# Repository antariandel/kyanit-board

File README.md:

# __Kyanit__ Board

## Introduction

Kyanit Board is part of the Kyanit ecosystem. See https://github.com/kyanit-project/kyanit for an
introduction to Kyanit.

Kyanit Board is the official Kyanit Core-compatible ESP8266-based controller board designed to be
used for home automation.

## The Kyanit Ecosystem

* [**Kyanit Core**](https://github.com/kyanit-project/kyanit)

The core Kyanit module, flashed into an ESP8266 board.

* [**Kyanit Board**](https://github.com/kyanit-project/kyanit-board)

This repo. A stylish, triangle-shaped ESP8266-based board built around an ESP-12F module, the
official Kyanit controller board.

* [**Kyanit CTL**](https://github.com/kyanit-project/kyanit-ctl)

Command-line utility for interacting with Kyanit.

* [**Kyanit API**](https://github.com/kyanit-project/kyanit-api)

Python API for interaction with Kyanit from Python code. (It is used by Kyanit CTL.)

## Board Files

The board is designed in KiCAD and is currently under development. First release to come soon...

## License Notice

Copyright (C) 2020 Zsolt Nagy

This program is free software: you can redistribute it and/or modify it under the terms of the
GNU General Public License as published by the Free Software Foundation, version 3 of the License.

This program is distributed in the hope that it will be useful, but WITHOUT ANY WARRANTY; without
even the implied warranty of MERCHANTABILITY or FITNESS FOR A PARTICULAR PURPOSE.
See the GNU General Public License for more details.
You should have received a copy of the GNU General Public License along with this program.
If not, see <https://www.gnu.org/licenses/>.

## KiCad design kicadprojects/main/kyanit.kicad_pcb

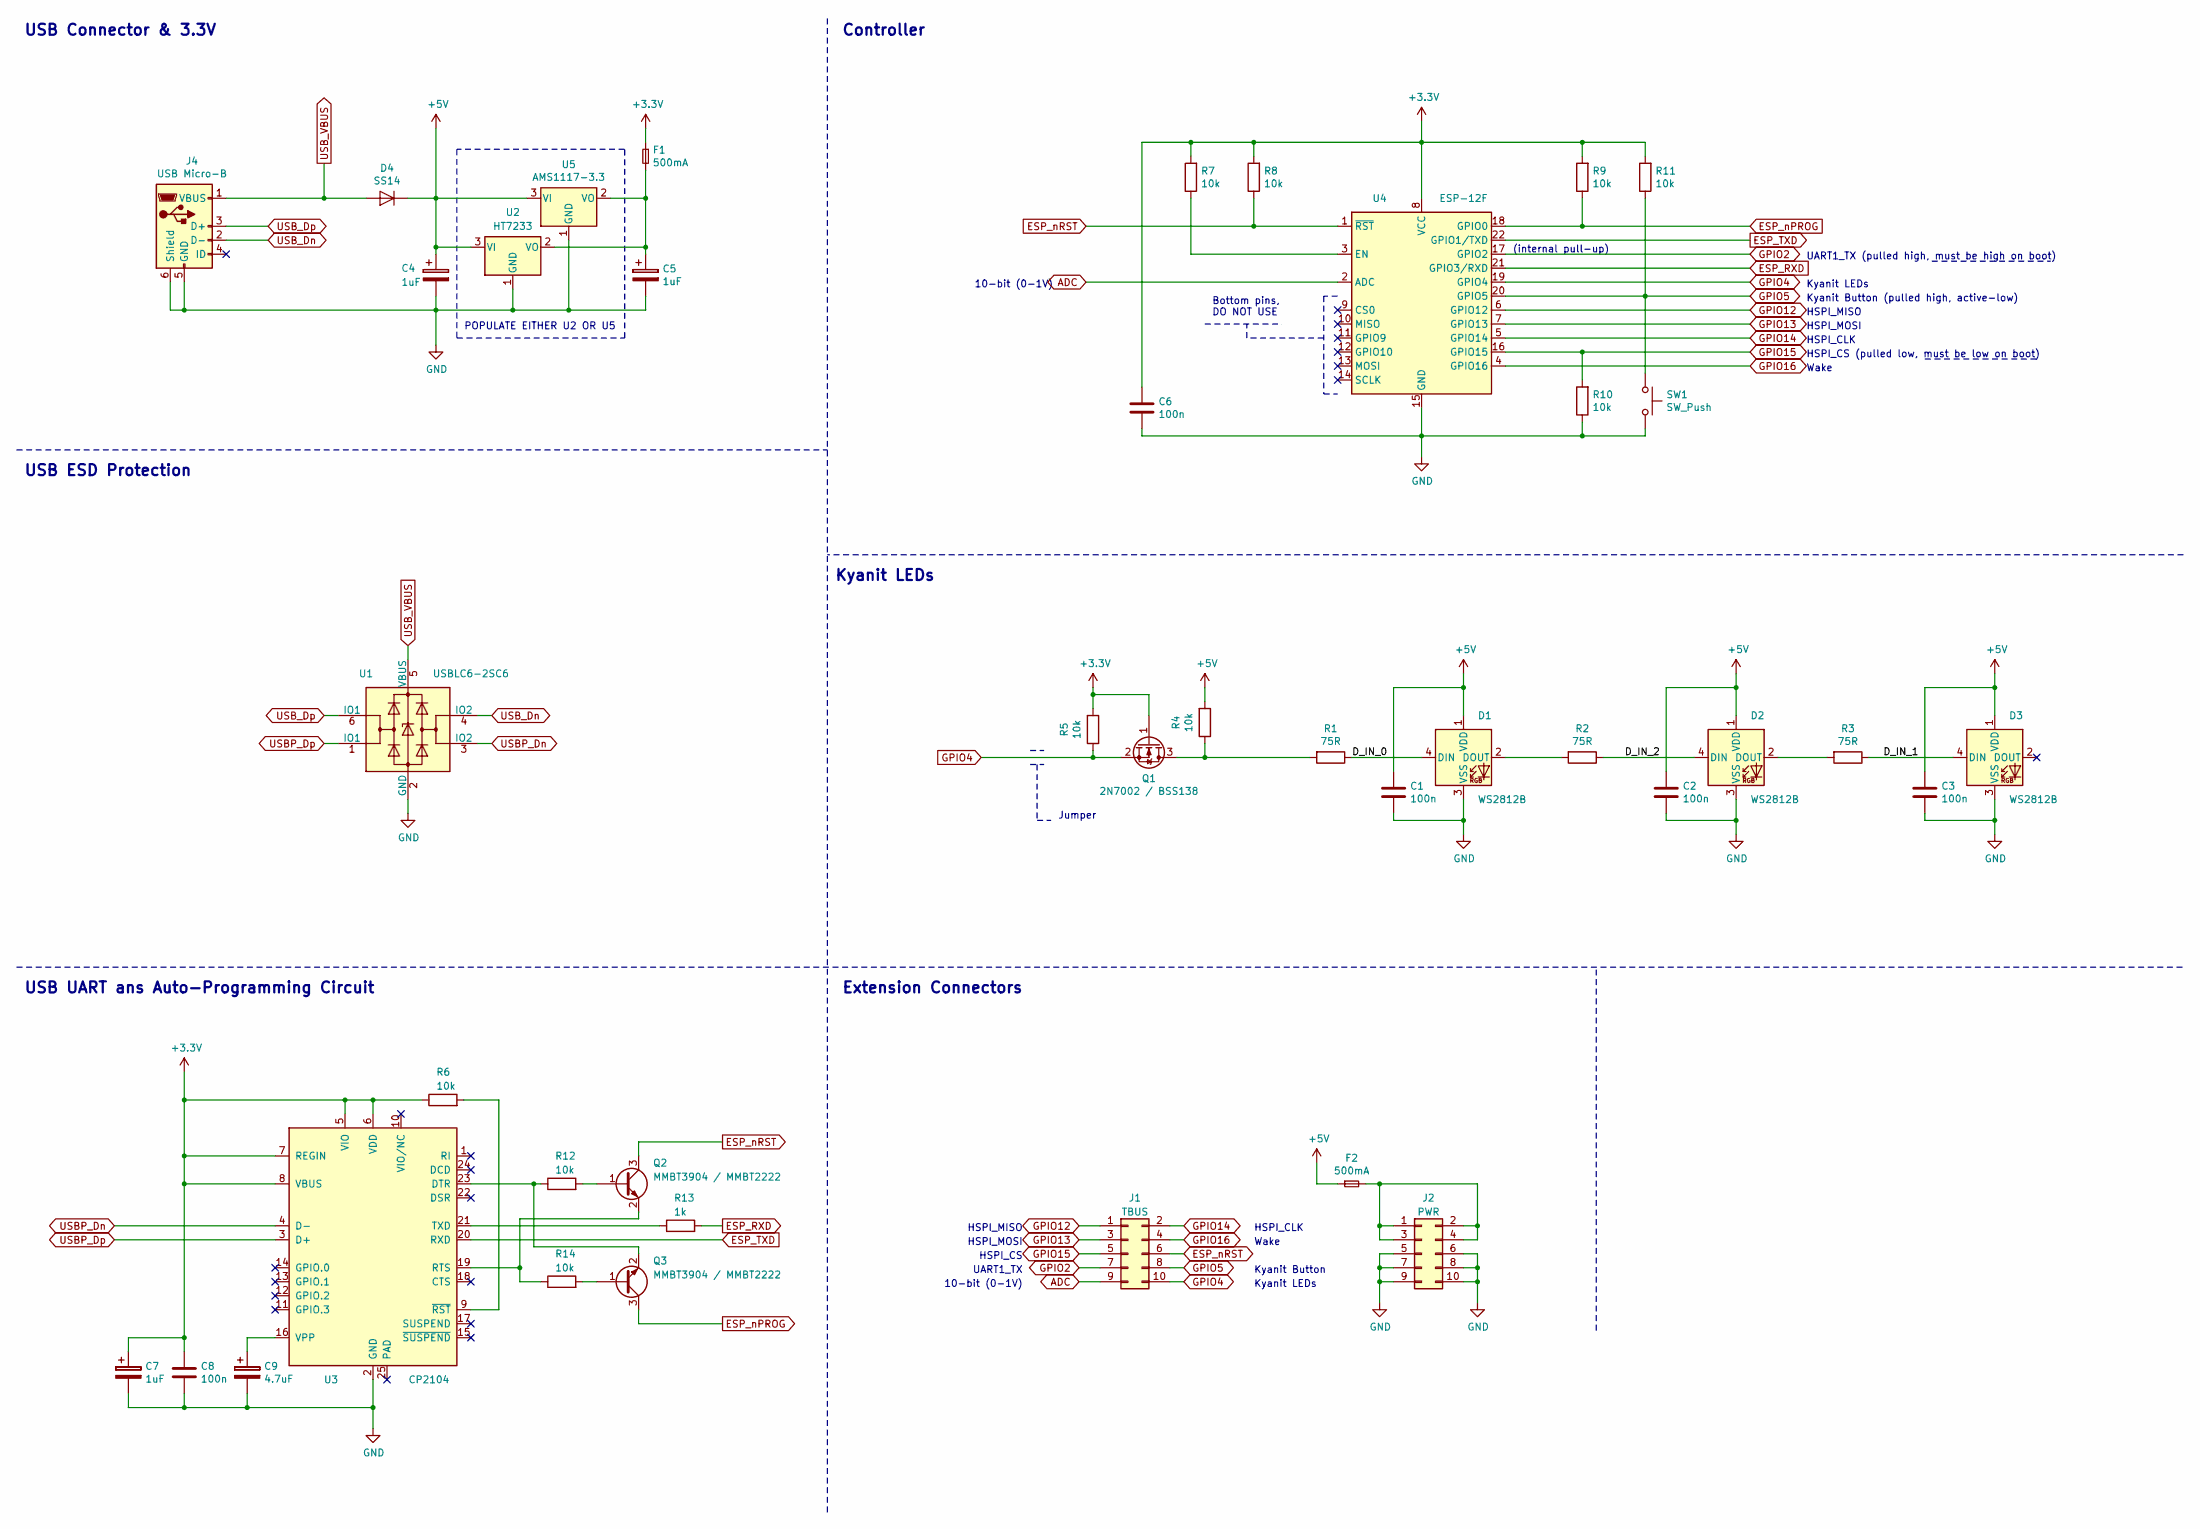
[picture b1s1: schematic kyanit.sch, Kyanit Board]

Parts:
C1, C2, C3, C6, C8: 100n; C_0603_1608Metric_Pad1.05x0.95mm_HandSolder
C4, C5, C7: 1uF; C_1206_3216Metric_Pad1.42x1.75mm_HandSolder
C9: 4.7uF; C_1206_3216Metric_Pad1.42x1.75mm_HandSolder
D1, D2, D3: WS2812B; LED_WS2812B_PLCC4_5.0x5.0mm_P3.2mm
D4: SS14; D_SMA
F1, F2: 500mA; Fuse_1206_3216Metric_Pad1.42x1.75mm_HandSolder
J1: TBUS; PinHeader_2x05_P2.54mm_Vertical
J2: PWR; PinHeader_2x05_P2.54mm_Vertical
J4: USB Micro-B; USB_Micro-B_Molex_47346-0001
Q1: 2N7002 / BSS138; SOT-23
Q2, Q3: MMBT3904 / MMBT2222; SOT-23
R1, R2, R3: 75R; R_0603_1608Metric_Pad1.05x0.95mm_HandSolder
R4, R5, R6, R7, R8, R9, R10, R11, R12, R14: 10k; R_0603_1608Metric_Pad1.05x0.95mm_HandSolder
R13: 1k; R_0603_1608Metric_Pad1.05x0.95mm_HandSolder
SW1: SW_Push; SW_SPST_EVPBF
U1: USBLC6-2SC6; SOT-23-6
U2: HT7233; SOT-23
U3: CP2104; QFN-24-1EP_4x4mm_P0.5mm_EP2.6x2.6mm
U4: ESP-12F; ESP-12E
U5: AMS1117-3.3; SOT-223-3_TabPin2

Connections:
+3V3: C6.1, C7.1, C8.1, F1.1, Q1.1 (G), R5.2, R6.1, R7.2, R8.2, R9.2, R11.2, U3.5 (VIO), U3.6 (VDD), U3.7 (REGIN), U3.8 (VBUS), U4.8 (VCC)
+5V: C1.1, C2.1, C3.1, C4.1, D1.1 (VDD), D2.1 (VDD), D3.1 (VDD), D4.1 (K), F2.1, R4.2, U2.3 (VI), U5.3 (VI)
/D_IN_0: D1.4 (DIN), R1.1
/D_IN_1: D3.4 (DIN), R3.1
/D_IN_2: D2.4 (DIN), R2.1
ADC: J1.9, U4.2 (ADC)
ESP_RXD: R13.2, U4.21 (GPIO3/RXD)
ESP_TXD: U3.20 (RXD), U4.22 (GPIO1/TXD)
ESP_nPROG: Q3.3 (C), R9.1, U4.18 (GPIO0)
ESP_nRST: J1.6, Q2.3 (C), R8.1, U4.1 (~RST)
GND: C1.2, C2.2, C3.2, C4.2, C5.2, C6.2, C7.2, C8.2, C9.2, D1.3 (VSS), D2.3 (VSS), D3.3 (VSS), J2.5, J2.6, J2.7, J2.8, J2.9, J2.10, J4.5 (GND), J4.6 (Shield), R10.1, SW1.2, U1.2 (GND), U2.1 (GND), U3.2 (GND), U4.15 (GND), U5.1 (GND)
GPIO2: J1.7, U4.17 (GPIO2)
GPIO4: J1.10, Q1.2 (S), R5.1, U4.19 (GPIO4)
GPIO5: J1.8, R11.1, SW1.1, U4.20 (GPIO5)
GPIO12: J1.1, U4.6 (GPIO12)
GPIO13: J1.3, U4.7 (GPIO13)
GPIO14: J1.2, U4.5 (GPIO14)
GPIO15: J1.5, R10.2, U4.16 (GPIO15)
GPIO16: J1.4, U4.4 (GPIO16)
unnamed: C5.1, F1.2, U2.2 (VO), U5.2 (VO)
unnamed: C9.1, U3.16 (VPP)
unnamed: D1.2 (DOUT), R2.2
unnamed: D2.2 (DOUT), R3.2
unnamed: F2.2, J2.1, J2.2, J2.3, J2.4
unnamed: Q1.3 (D), R1.2, R4.1
unnamed: Q2.1 (B), R12.2
unnamed: Q2.2 (E), R14.1, U3.19 (RTS)
unnamed: Q3.1 (B), R14.2
unnamed: Q3.2 (E), R12.1, U3.23 (DTR)
unnamed: R6.2, U3.9 (~RST)
unnamed: R7.1, U4.3 (EN)
unnamed: R13.1, U3.21 (TXD)
USBP_Dn: U1.3 (IO2), U3.4 (D-)
USBP_Dp: U1.1 (IO1), U3.3 (D+)
USB_Dn: J4.2 (D-), U1.4 (IO2)
USB_Dp: J4.3 (D+), U1.6 (IO1)
USB_VBUS: D4.2 (A), J4.1 (VBUS), U1.5 (VBUS)

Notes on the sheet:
USB Connector & 3.3V
USB ESD Protection
USB UART ans Auto-Programming Circuit
Extension Connectors
Kyanit LEDs
Controller
UART1_TX (pulled high, must be high on boot)
Kyanit Button (pulled high, active-low)
HSPI_MISO
HSPI_MOSI
HSPI_CLK
HSPI_CS (pulled low, must be low on boot)
10-bit (0-1V)
Bottom pins, DO NOT USE
(internal pull-up)
Wake
HSPI_CS
UART1_TX
Kyanit Button
Jumper
POPULATE EITHER U2 OR U5

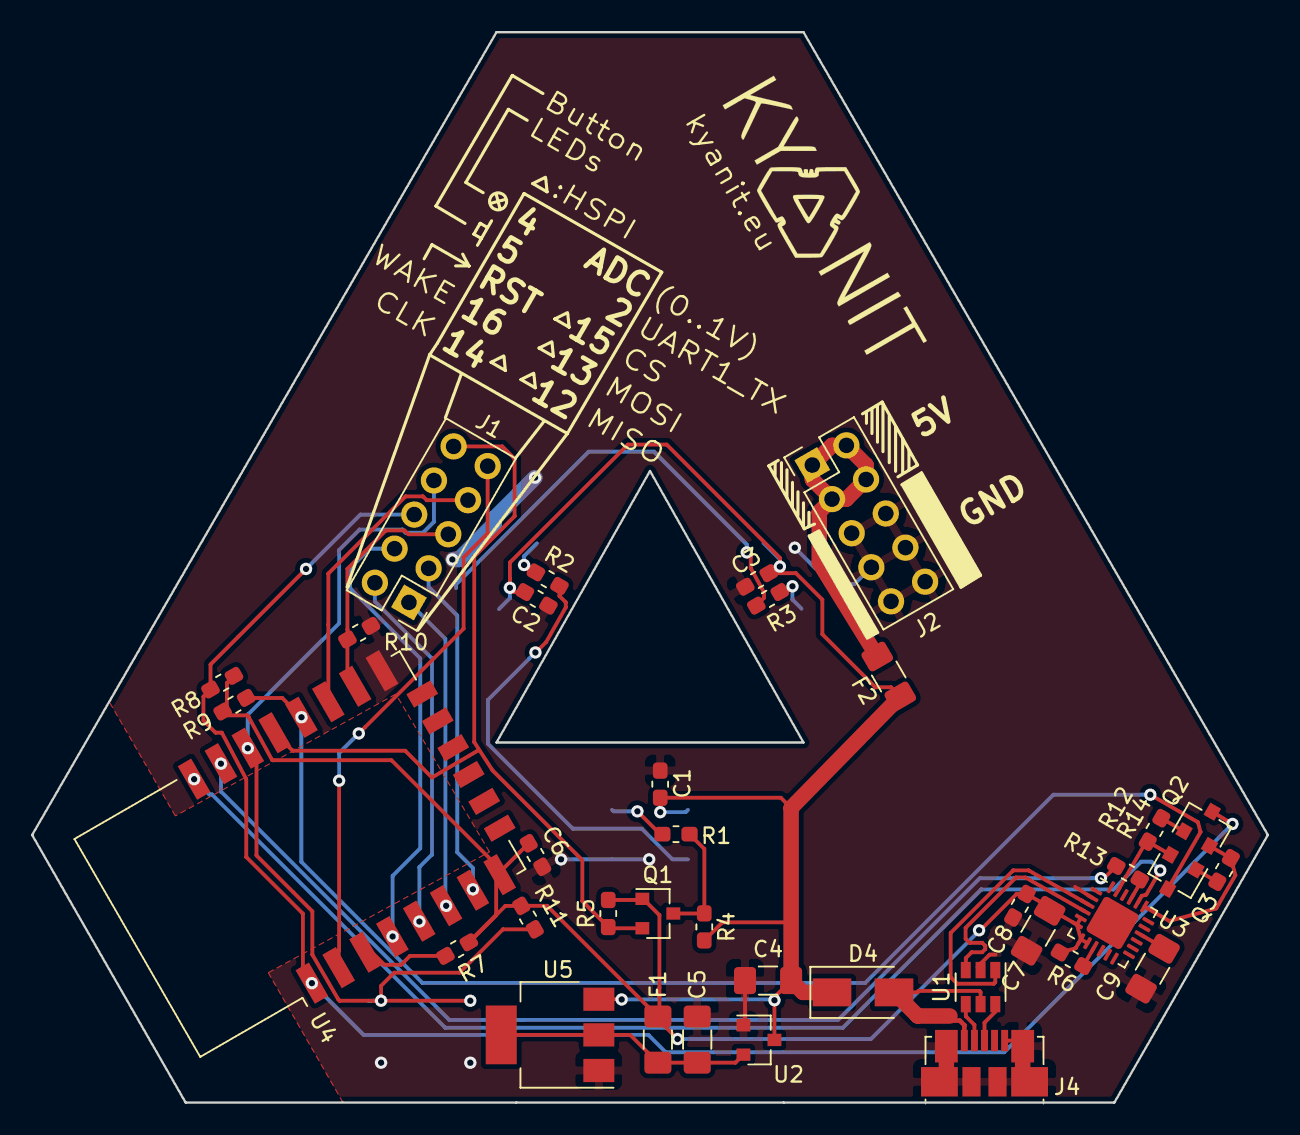
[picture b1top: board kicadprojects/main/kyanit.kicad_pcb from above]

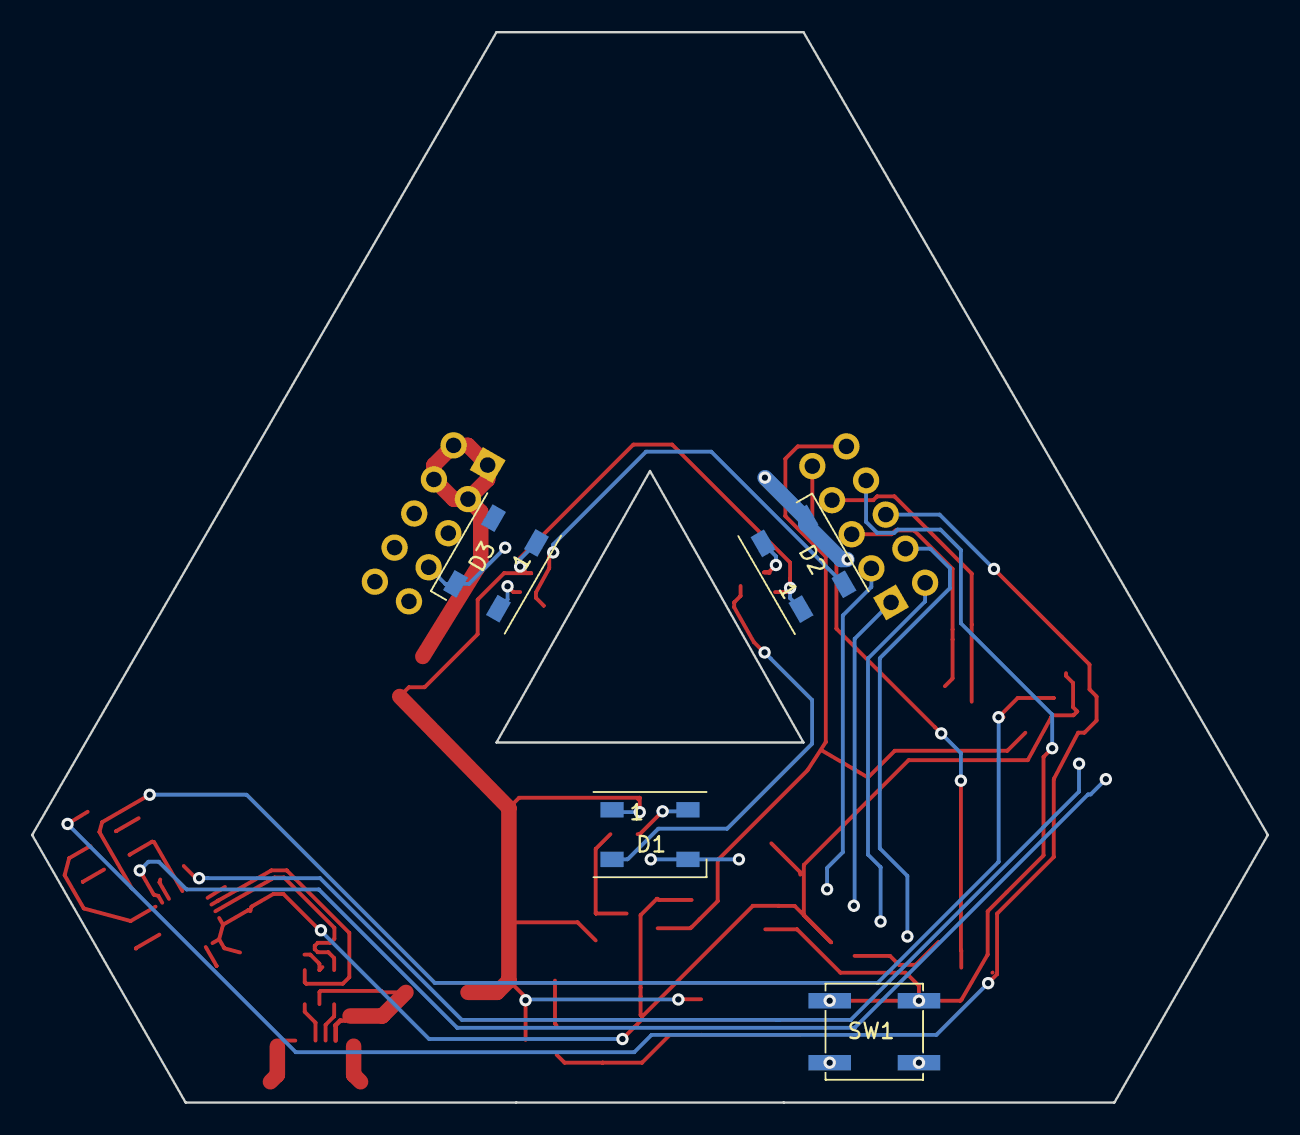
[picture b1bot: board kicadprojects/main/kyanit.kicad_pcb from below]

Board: 2 copper layers, 79.8 x 69.1 mm, 41 parts (4 on the bottom side), 37 nets.

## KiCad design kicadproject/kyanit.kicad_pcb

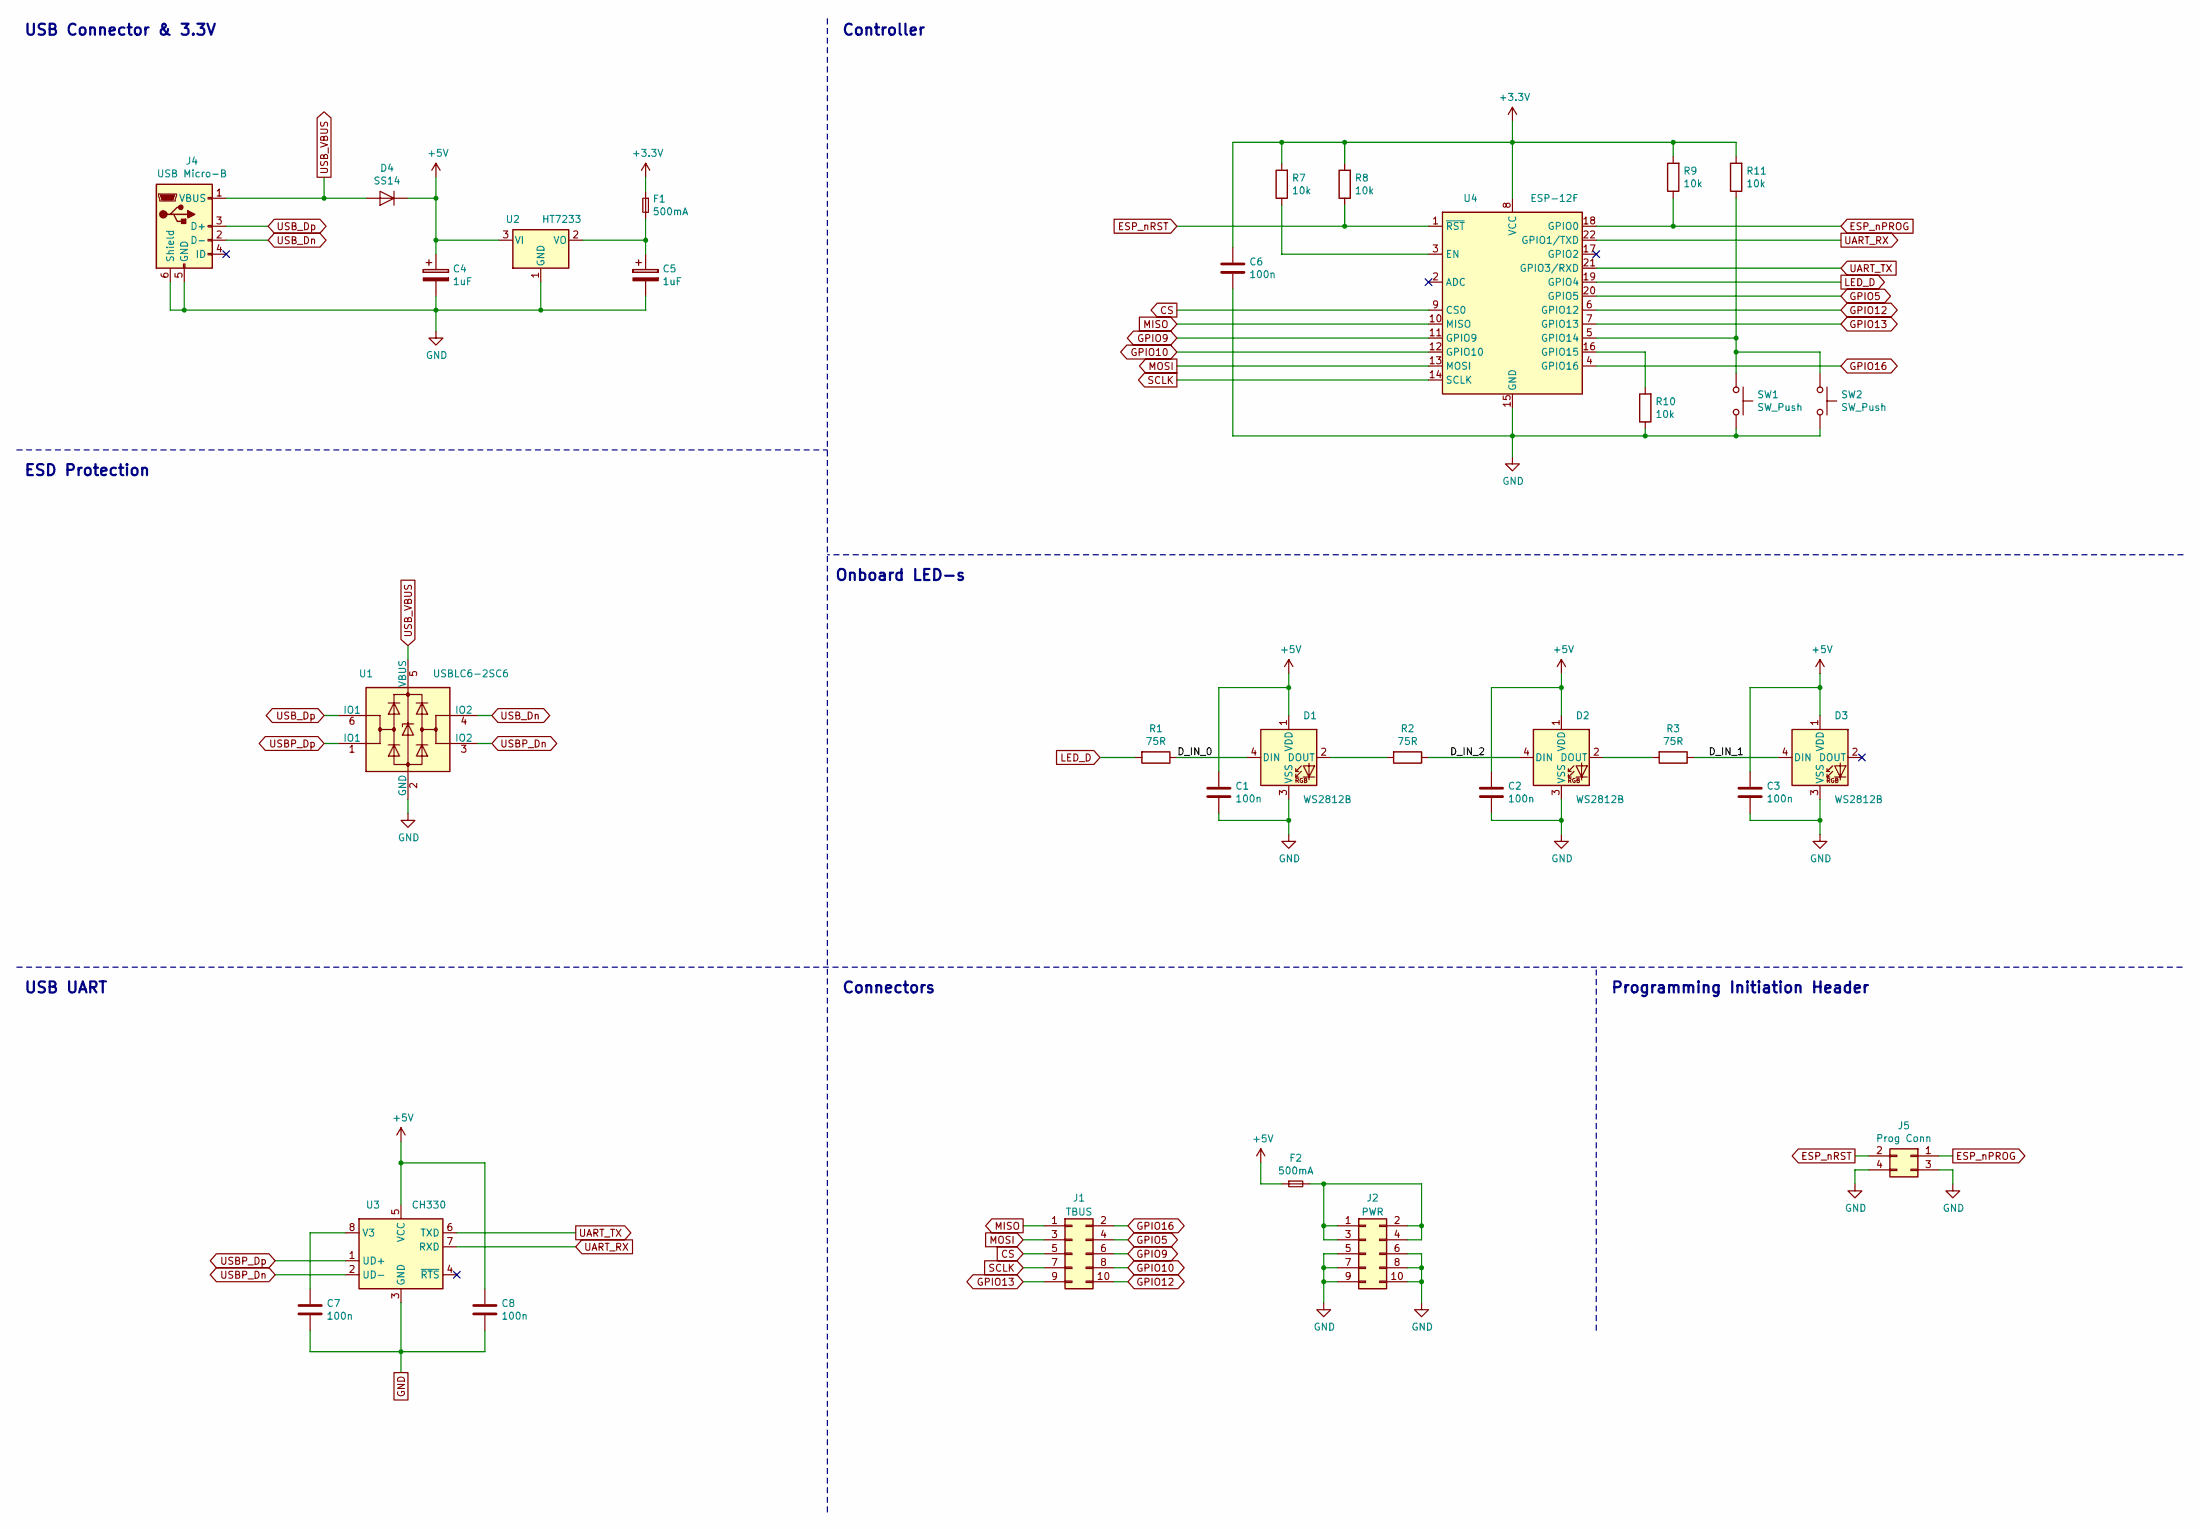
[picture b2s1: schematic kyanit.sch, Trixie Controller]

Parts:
C1, C2, C3, C6, C7, C8: 100n; C_0603_1608Metric_Pad1.05x0.95mm_HandSolder
C4, C5: 1uF; C_1206_3216Metric_Pad1.42x1.75mm_HandSolder
D1, D2, D3: WS2812B; LED_WS2812B_PLCC4_5.0x5.0mm_P3.2mm
D4: SS14; D_SMA
F1, F2: 500mA; Fuse_1206_3216Metric_Pad1.42x1.75mm_HandSolder
J1: TBUS; PinHeader_2x05_P2.54mm_Vertical
J2: PWR; PinHeader_2x05_P2.54mm_Vertical
J4: USB Micro-B; USB_Micro-B_Molex_47346-0001
J5: Prog Conn; PinHeader_2x02_P2.00mm_Vertical_SMD
R1, R2, R3: 75R; R_0603_1608Metric_Pad1.05x0.95mm_HandSolder
R7, R8, R9, R10, R11: 10k; R_0603_1608Metric_Pad1.05x0.95mm_HandSolder
SW1, SW2: SW_Push; SW_SPST_EVPBF
U1: USBLC6-2SC6; SOT-23-6
U2: HT7233; SOT-23
U3: CH330; SOIC-8_3.9x4.9mm_P1.27mm
U4: ESP-12F; ESP-12E

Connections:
+3V3: C6.1, F1.1, R7.2, R8.2, R9.2, R11.2, U4.8 (VCC)
+5V: C1.1, C2.1, C3.1, C4.1, C8.1, D1.1 (VDD), D2.1 (VDD), D3.1 (VDD), D4.1 (K), F2.1, U2.3 (VI), U3.5 (VCC)
/D_IN_0: D1.4 (DIN), R1.1
/D_IN_1: D3.4 (DIN), R3.1
/D_IN_2: D2.4 (DIN), R2.1
CS: J1.5, U4.9 (CS0)
ESP_nPROG: J5.1, R9.1, U4.18 (GPIO0)
ESP_nRST: J5.2, R8.1, U4.1 (~RST)
GND: C1.2, C2.2, C3.2, C4.2, C5.2, C6.2, C7.2, C8.2, D1.3 (VSS), D2.3 (VSS), D3.3 (VSS), J2.5, J2.6, J2.7, J2.8, J2.9, J2.10, J4.5 (GND), J4.6 (Shield), J5.3, J5.4, R10.1, SW1.2, SW2.2, U1.2 (GND), U2.1 (GND), U3.3 (GND), U4.15 (GND)
GPIO5: J1.4, U4.20 (GPIO5)
GPIO9: J1.6, U4.11 (GPIO9)
GPIO10: J1.8, U4.12 (GPIO10)
GPIO12: J1.10, U4.6 (GPIO12)
GPIO13: J1.9, U4.7 (GPIO13)
GPIO16: J1.2, U4.4 (GPIO16)
LED_D: R1.2, U4.19 (GPIO4)
MISO: J1.1, U4.10 (MISO)
MOSI: J1.3, U4.13 (MOSI)
unnamed: C5.1, F1.2, U2.2 (VO)
unnamed: C7.1, U3.8 (V3)
unnamed: D1.2 (DOUT), R2.2
unnamed: D2.2 (DOUT), R3.2
unnamed: F2.2, J2.1, J2.2, J2.3, J2.4
unnamed: R7.1, U4.3 (EN)
unnamed: R10.2, U4.16 (GPIO15)
unnamed: R11.1, SW1.1, SW2.1, U4.5 (GPIO14)
SCLK: J1.7, U4.14 (SCLK)
UART_RX: U3.7 (RXD), U4.22 (GPIO1/TXD)
UART_TX: U3.6 (TXD), U4.21 (GPIO3/RXD)
USBP_Dn: U1.3 (IO2), U3.2 (UD-)
USBP_Dp: U1.1 (IO1), U3.1 (UD+)
USB_Dn: J4.2 (D-), U1.4 (IO2)
USB_Dp: J4.3 (D+), U1.6 (IO1)
USB_VBUS: D4.2 (A), J4.1 (VBUS), U1.5 (VBUS)

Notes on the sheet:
USB Connector & 3.3V
ESD Protection
USB UART
Connectors
Onboard LED-s
Controller
Programming Initiation Header

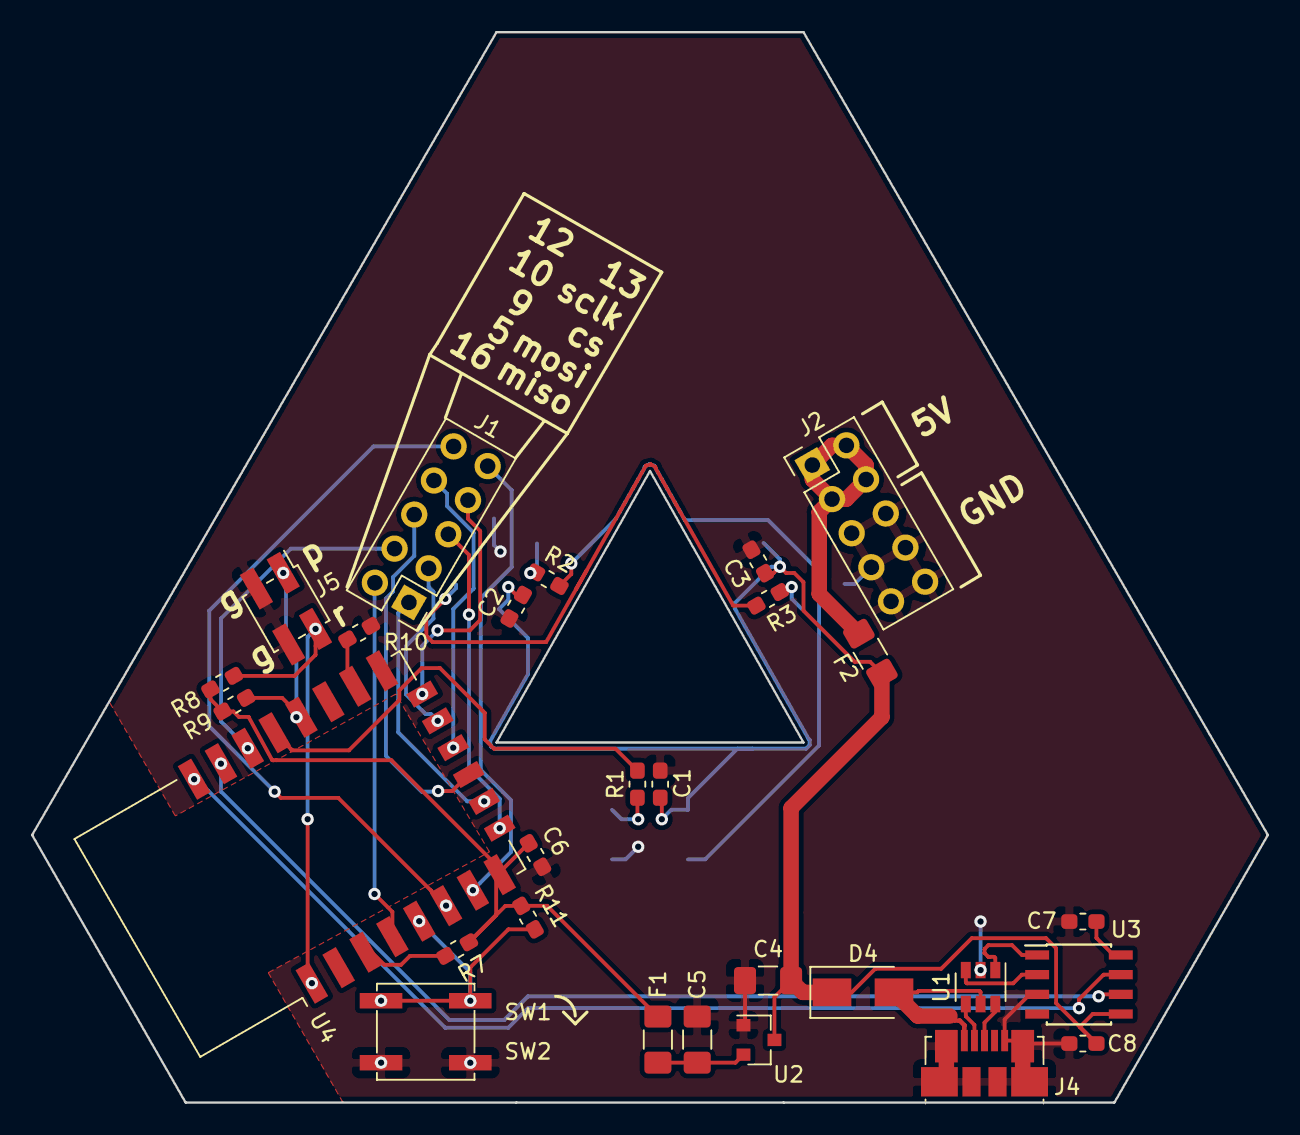
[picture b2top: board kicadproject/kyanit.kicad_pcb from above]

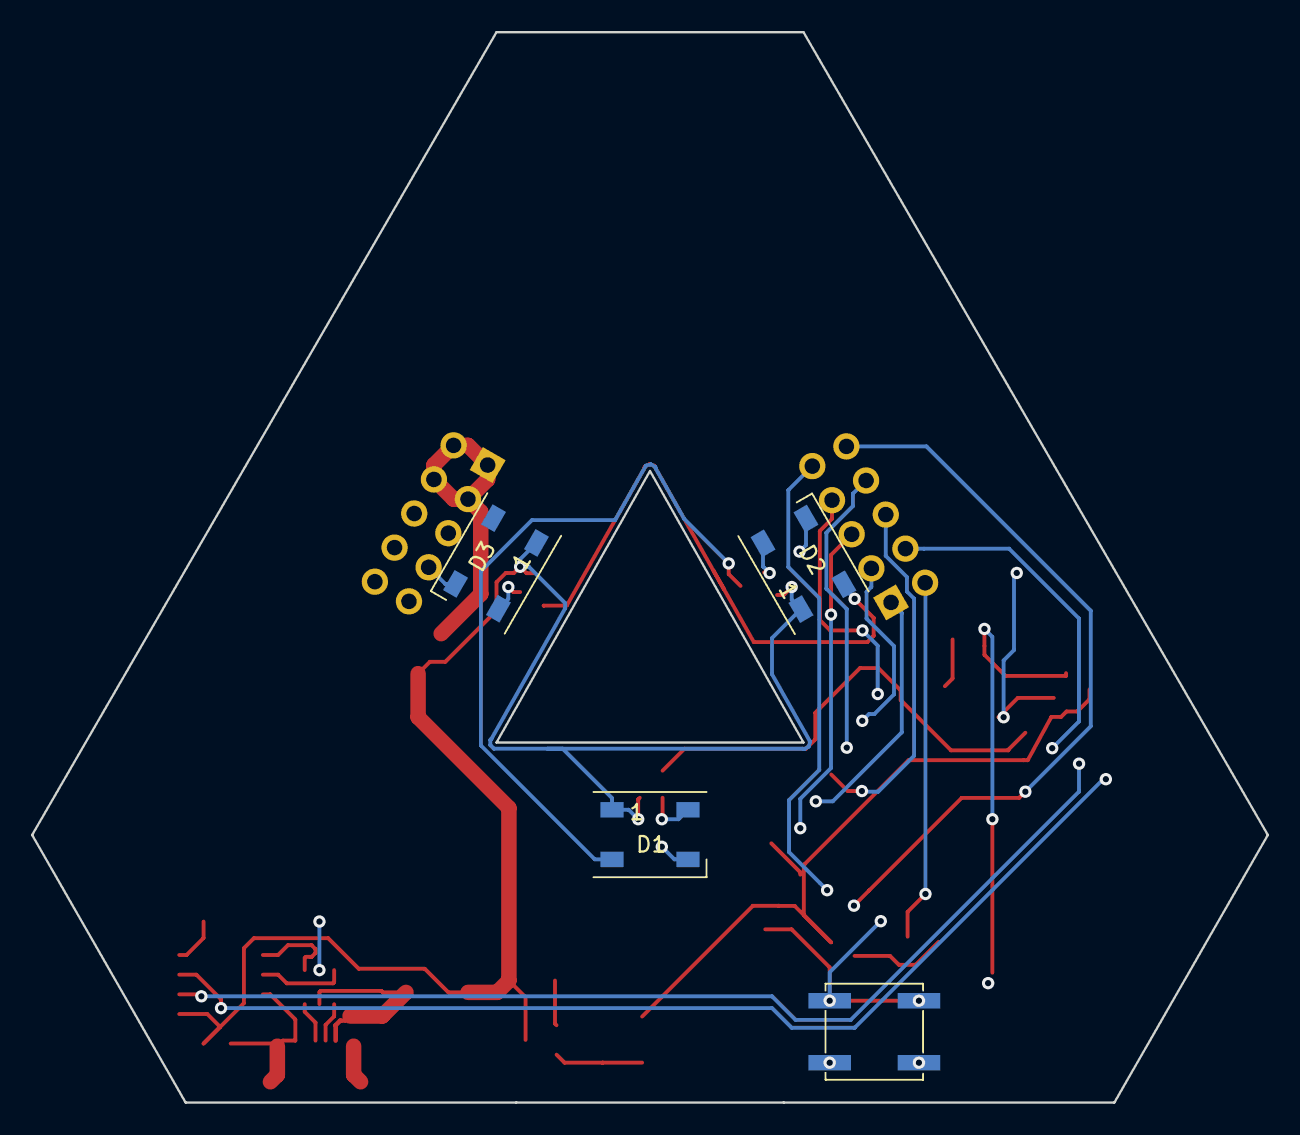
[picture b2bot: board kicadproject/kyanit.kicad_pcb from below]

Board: 2 copper layers, 79.8 x 69.1 mm, 32 parts (4 on the bottom side), 34 nets.

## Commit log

2020-03-30 initial: add Kyanit Board files
2020-03-30 docs: add README.md
2020-03-30 fix: fix 3dshapes and generate previews
2020-04-05 feat: rename gpio nets, add pinout to silkscreen
2020-04-05 chore: add .gitignore, remove backups
2020-04-05 fix: update layout (should have been commited with 3b8f99cb)
2020-10-01 feat!: add auto-program and proto board
